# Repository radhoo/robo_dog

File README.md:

# robo_dog
Develop user tracking technology and demo it using a rover robot to follow its user.

Project page: https://www.pocketmagic.net/make-the-robot-follow-you/

Demo video:

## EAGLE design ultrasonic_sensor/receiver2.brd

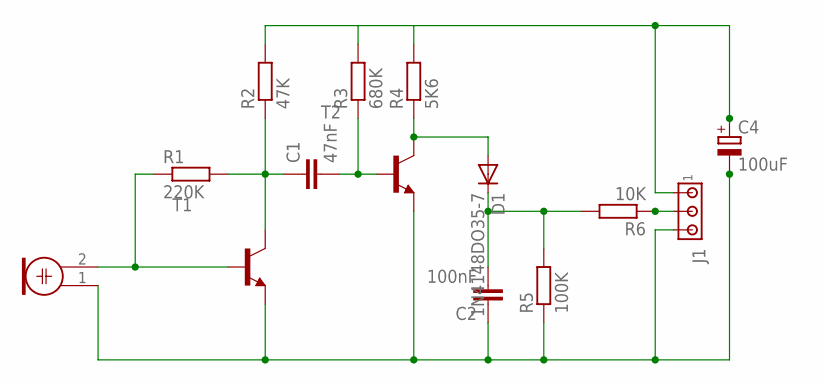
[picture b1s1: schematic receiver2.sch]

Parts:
C1: 47nF; C2.5-2
C2: 100nF; C2.5-2
C4: 100uF; B45181A
D1: 1N4148DO35-7; DO35-7
J1: MTA03-100; 10X03MTA
M1: ELECTRET_MICROPHON-F6050AP; F6050AP
R1: 220K; 0207/10
R2: 47K; 0207/10
R3: 680K; 0207/10
R4: 5K6; 0207/10
R5: 100K; 0207/10
R6: 10K; 0207/10
T1, T2: BC548-NPN-TO92-CBE; TO92-CBE

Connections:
unnamed: M1.2, R1.1, T1.B
unnamed: C1.1, R1.2, R2.1, T1.C
unnamed: C2.1, C4.-, J1.3, M1.1, R5.1, T1.E, T2.E
unnamed: C1.2, R3.1, T2.B
unnamed: D1.A, R4.1, T2.C
unnamed: C4.+, J1.1, R2.2, R3.2, R4.2
unnamed: C2.2, D1.C, R5.2, R6.2
unnamed: J1.2, R6.1

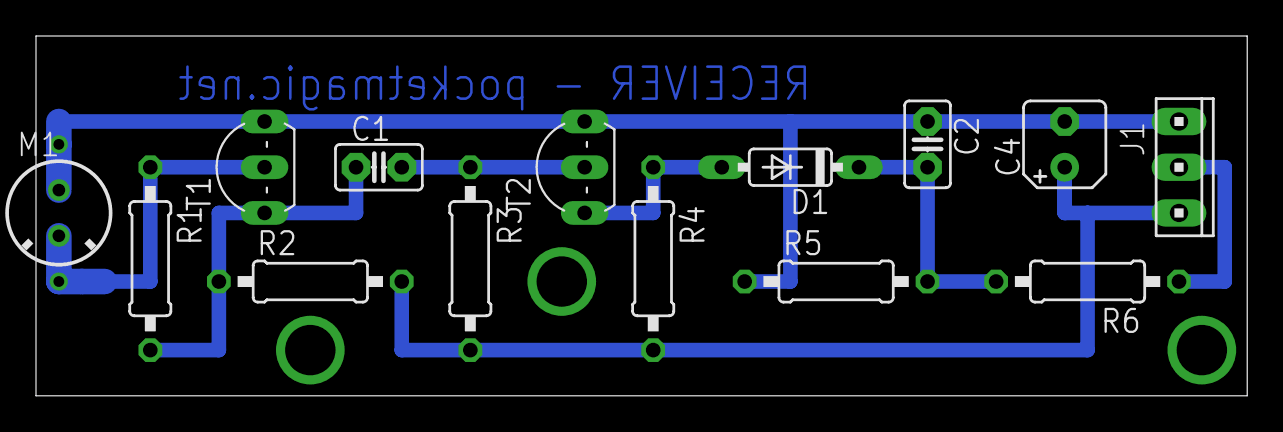
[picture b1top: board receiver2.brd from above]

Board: 2 copper layers, 67.3 x 20.0 mm, 14 parts (0 on the bottom side), 8 nets.

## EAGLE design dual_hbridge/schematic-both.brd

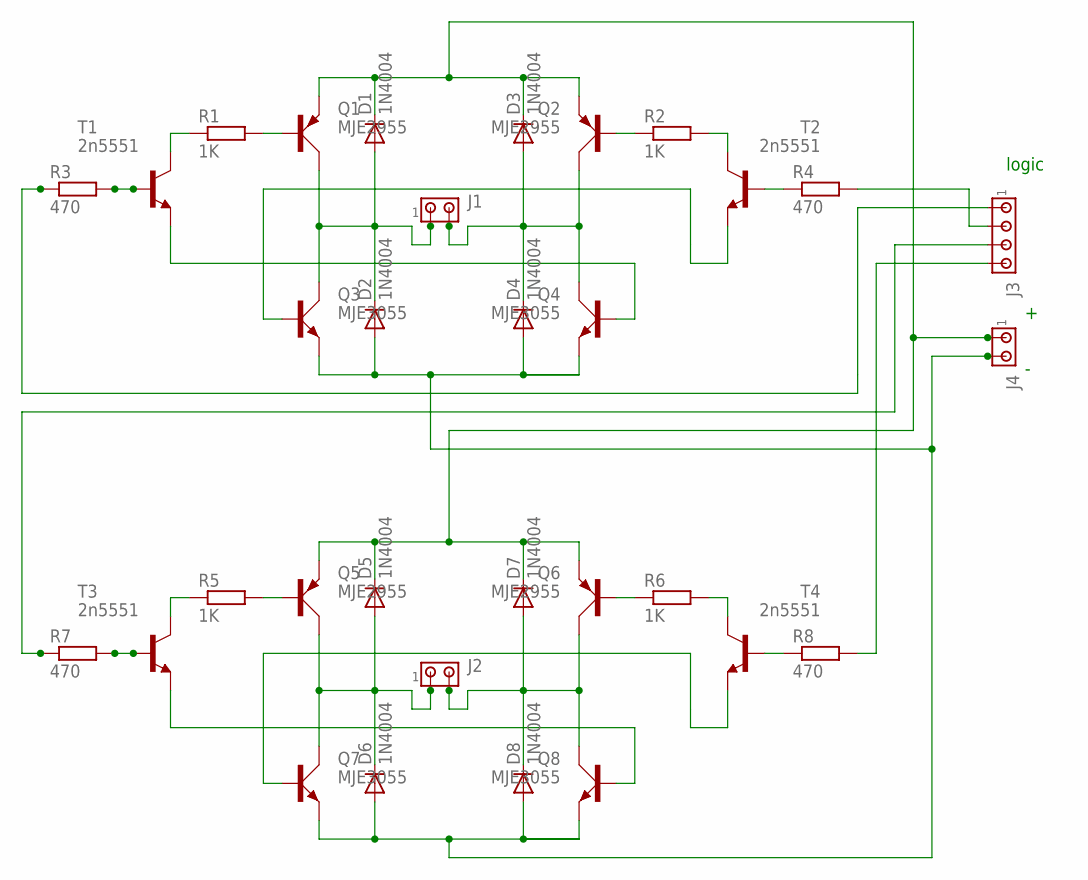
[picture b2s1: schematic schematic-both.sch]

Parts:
D1, D2, D3, D4, D5, D6, D7, D8: 1N4004; DO41-10
J1, J2, J4: MTA02-156; 1X2MTA
J3: MTA04-100; 10X04MTA
Q1, Q2, Q5, Q6: MJE2955; TO220AV
Q3, Q4, Q7, Q8: MJE3055; TO220AV
R1, R2, R5, R6: 1K; 0204/7
R3, R4, R7, R8: 470; 0204/7
T1, T2, T3, T4: 2n5551; TO92-EBC

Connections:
unnamed: J3.2, R4.2
unnamed: D1.A, D2.C, J1.1, Q1.C, Q3.C
unnamed: R1.1, T1.C
unnamed: Q1.B, R1.2
unnamed: D3.A, D4.C, J1.2, Q2.C, Q4.C
unnamed: Q2.B, R2.1
unnamed: R2.2, T2.C
unnamed: D1.C, D3.C, D5.C, D7.C, J4.1, Q1.E, Q2.E, Q5.E, Q6.E
unnamed: Q3.B, T2.E
unnamed: D5.A, D6.C, J2.1, Q5.C, Q7.C
unnamed: R3.2, T1.B
unnamed: R4.1, T2.B
unnamed: Q4.B, T1.E
unnamed: D2.A, D4.A, D6.A, D8.A, J4.2, Q3.E, Q4.E, Q7.E, Q8.E
unnamed: D7.A, D8.C, J2.2, Q6.C, Q8.C
unnamed: R5.1, T3.C
unnamed: Q5.B, R5.2
unnamed: Q6.B, R6.1
unnamed: Q7.B, T4.E
unnamed: R6.2, T4.C
unnamed: R7.2, T3.B
unnamed: R8.1, T4.B
unnamed: Q8.B, T3.E
unnamed: J3.1, R3.1
unnamed: J3.4, R8.2
unnamed: J3.3, R7.1

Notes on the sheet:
logic

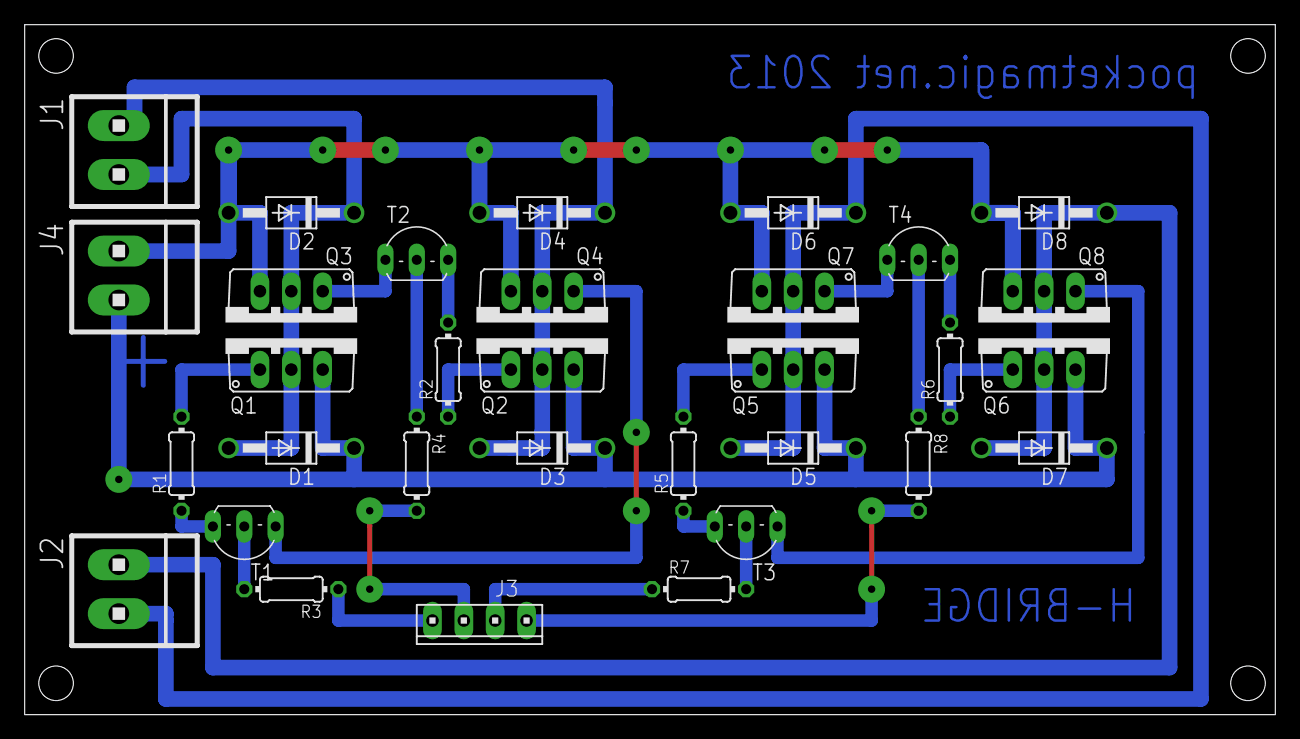
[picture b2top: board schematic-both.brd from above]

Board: 2 copper layers, 101.3 x 55.9 mm, 32 parts (0 on the bottom side), 26 nets.

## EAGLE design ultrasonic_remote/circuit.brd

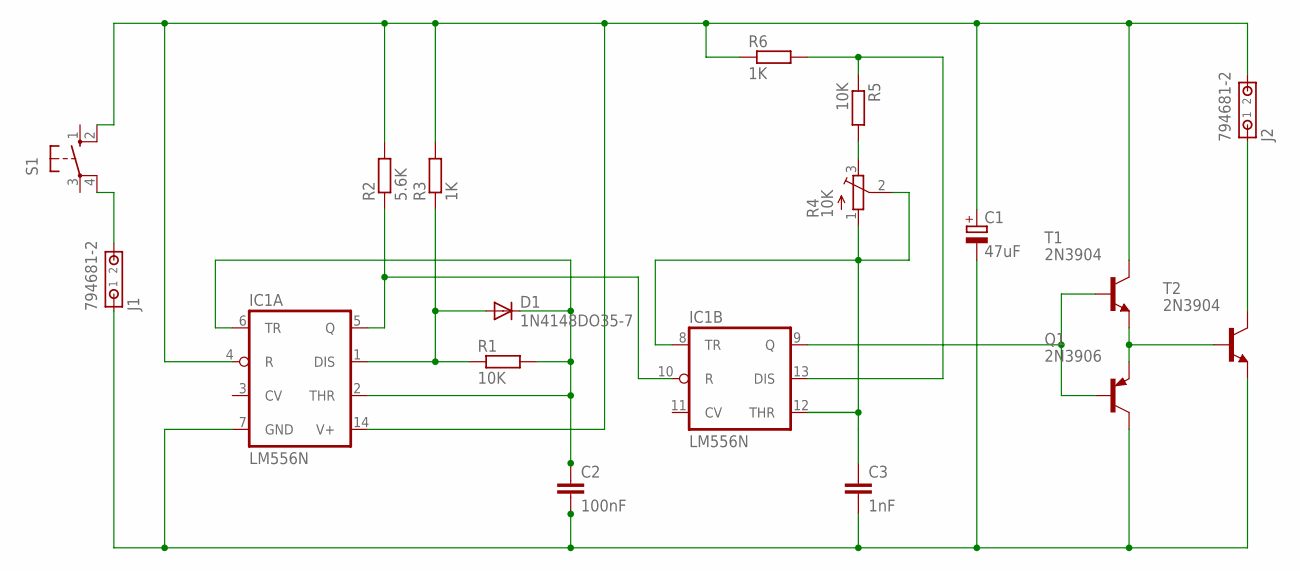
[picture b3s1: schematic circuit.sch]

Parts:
C1: 47uF; B45181B
C2: 100nF; C0805
C3: 1nF; C0805
D1: 1N4148DO35-7; DO35-7
IC1: LM556N; DIL14
J1, J2: 794681-2
Q1: 2N3906; TO92
R1, R5: 10K; R0805
R2: 5.6K; R0805
R3, R6: 1K; R0805
R4: 10K; 3223J
S1: 10-XX; B3F-10XX
T1, T2: 2N3904; TO92

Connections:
unnamed: C1.+, IC1.4 (R), IC1.14 (V+), J2.2, R2.2, R3.2, R6.1, S1.2 (S1), T1.1 (C)
unnamed: IC1.5 (Q), IC1.10 (R), R2.1
unnamed: C1.-, C2.2, C3.2, IC1.7 (GND), J1.1, Q1.1 (C), T2.3 (E)
unnamed: C2.1, D1.C, IC1.2 (THR), IC1.6 (TR), R1.2
unnamed: D1.A, IC1.1 (DIS), R1.1, R3.1
unnamed: C3.1, IC1.8 (TR), IC1.12 (THR), R4.1 (A), R4.2 (S)
unnamed: R4.3 (E), R5.2
unnamed: IC1.13 (DIS), R5.1, R6.2
unnamed: IC1.9 (Q), Q1.2 (B), T1.2 (B)
unnamed: Q1.3 (E), T1.3 (E), T2.2 (B)
unnamed: J2.1, T2.1 (C)
unnamed: J1.2, S1.4 (P1)

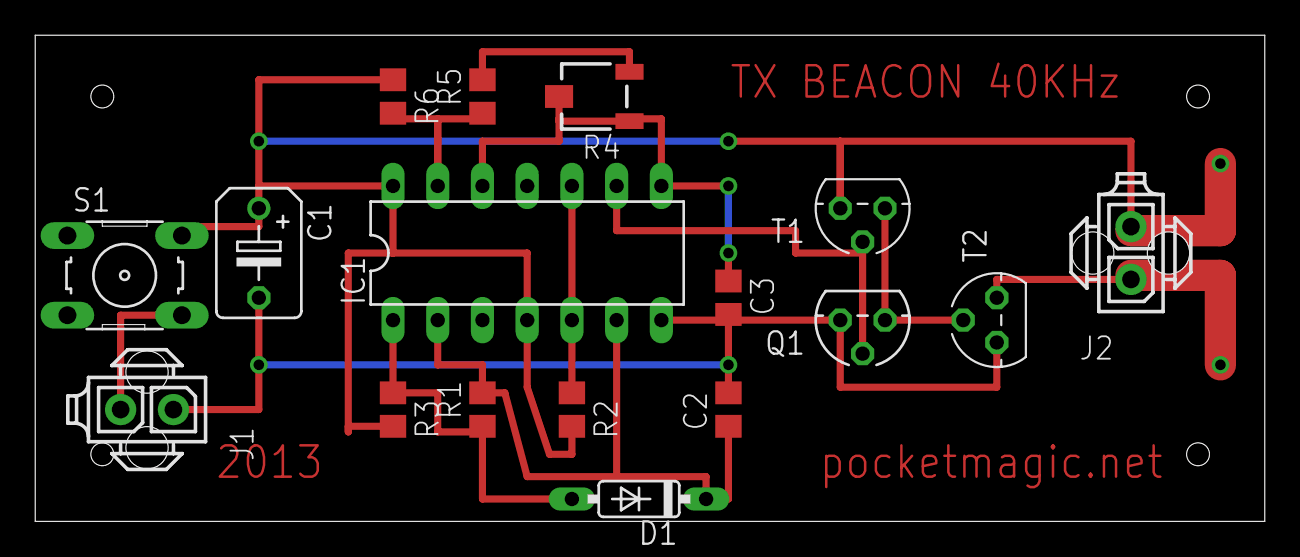
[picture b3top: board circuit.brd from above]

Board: 2 copper layers, 69.8 x 27.6 mm, 17 parts (0 on the bottom side), 12 nets.

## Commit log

2017-07-16 Source code released as open source
